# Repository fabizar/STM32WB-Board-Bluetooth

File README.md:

# KiCad Project: [STM32WB Board Bluetooth]

This is a hardware design project created using **KiCad**. It includes the schematic and PCB layout for a STM32 dev board.

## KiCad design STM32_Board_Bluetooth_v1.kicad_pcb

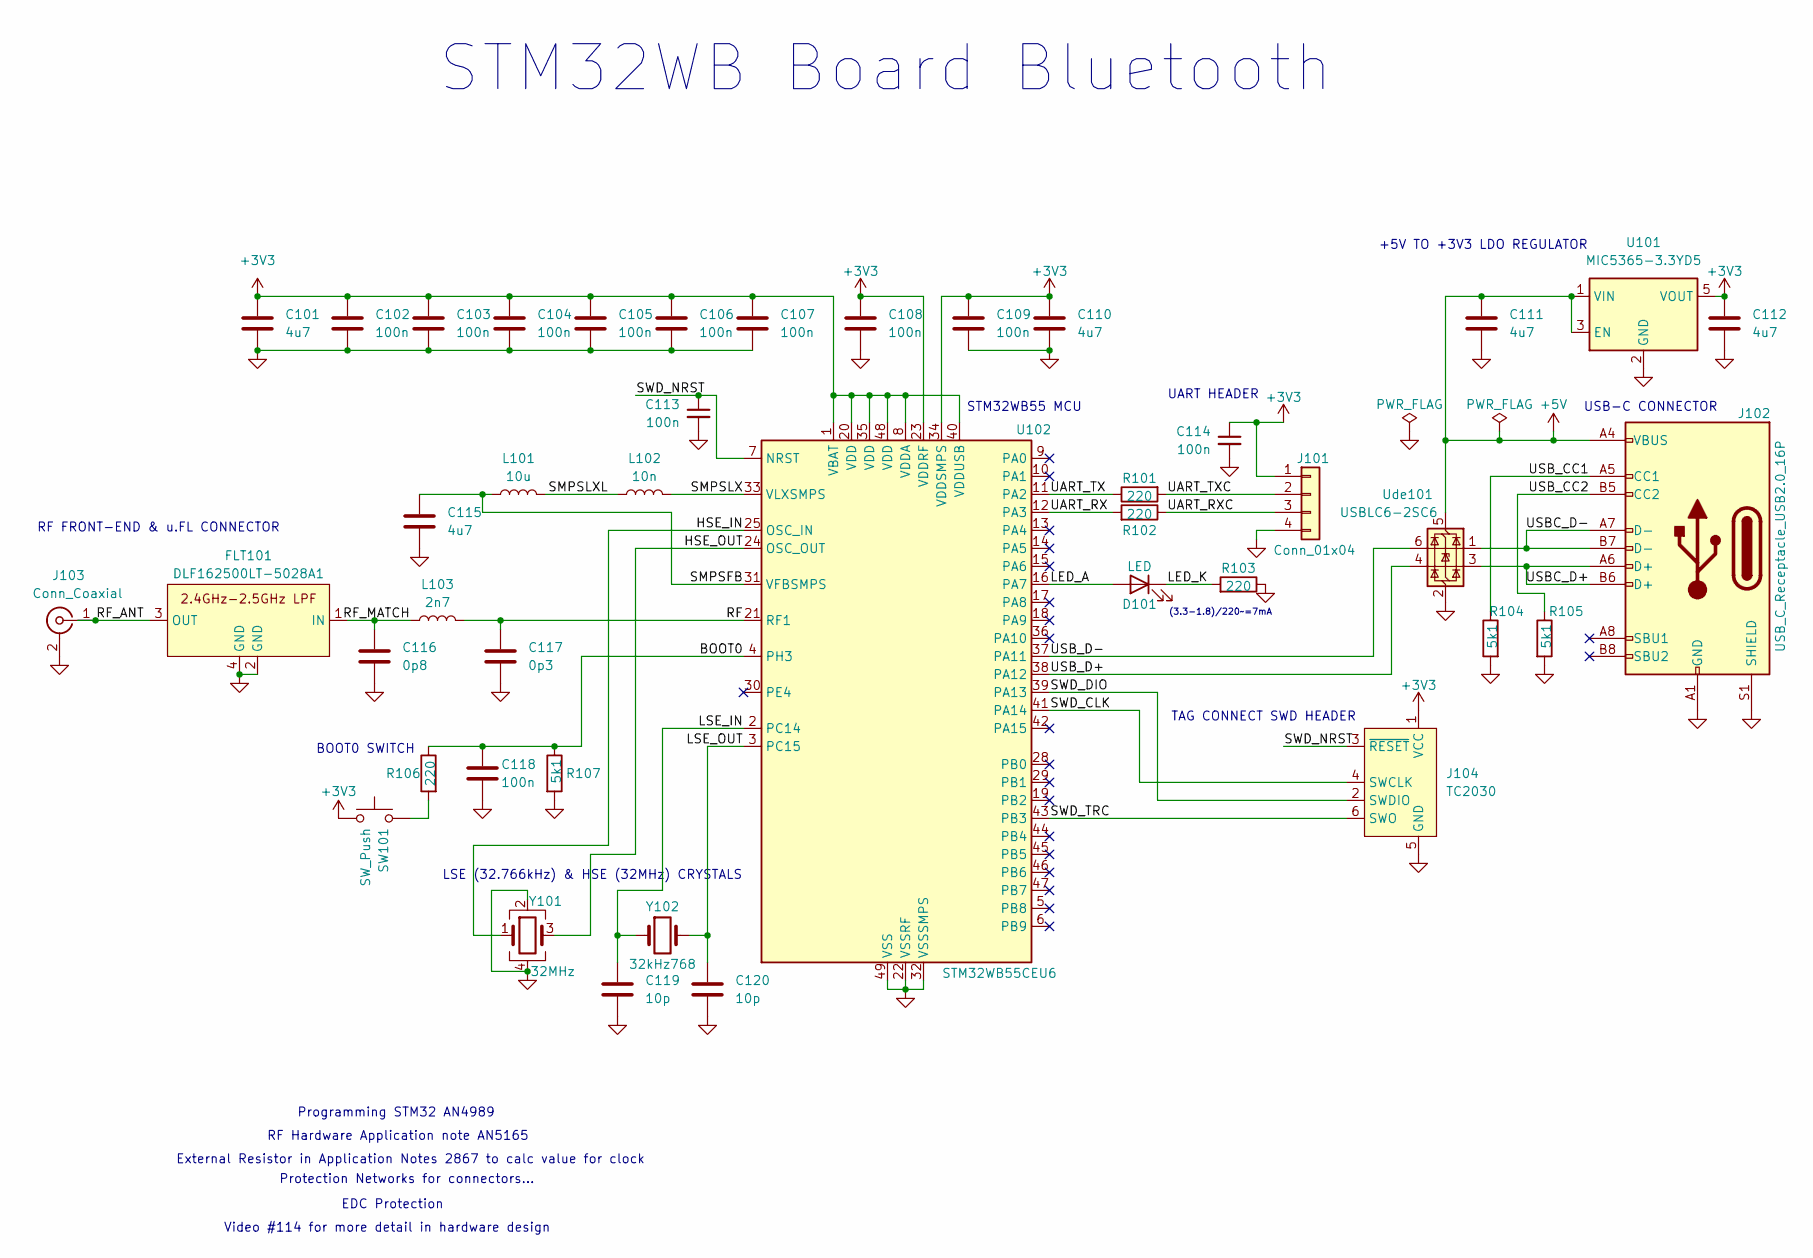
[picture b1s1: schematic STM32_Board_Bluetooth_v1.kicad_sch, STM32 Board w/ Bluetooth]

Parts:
C101, C110, C111, C112, C115: 4u7; C_0603_1608Metric
C102, C103, C104, C105, C106, C107, C108, C109, C113, C114, C118: 100n; C_0402_1005Metric
C116: 0p8; C_0402_1005Metric
C117: 0p3; C_0402_1005Metric
C119, C120: 10p; C_0402_1005Metric
D101: LED; LED_0402_1005Metric
FLT101: DLF162500LT-5028A1; DLT162500LT-5028A1
J101: Conn_01x04; Molex_PicoBlade_53048-0410_1x04_P1.25mm_Horizontal
J102: USB_C_Receptacle_USB2.0_16P; USB_C_Receptacle_GCT_USB4105-xx-A_16P_TopMnt_Horizontal
J103: Conn_Coaxial; U.FL_Hirose_U.FL-R-SMT-1_Vertical
J104: TC2030; Tag-Connect_TC2030-IDC-FP_2x03_P1.27mm_Vertical
L101: 10u; L_0805_2012Metric
L102: 10n; L_0402_1005Metric
L103: 2n7; L_0402_1005Metric
R101, R102, R103, R106: 220; R_0402_1005Metric
R104, R105, R107: 5k1; R_0402_1005Metric
SW101: SW_Push; SW_SPST_CK_RS282G05A3
U101: MIC5365-3.3YD5; SOT-23-5
U102: STM32WB55CEU6; QFN-48-1EP_7x7mm_P0.5mm_EP5.6x5.6mm
Ude101: USBLC6-2SC6; SOT-23-6
Y101: 32MHz; Crystal_SMD_2016-4Pin_2.0x1.6mm
Y102: 32kHz768; Crystal_SMD_2012-2Pin_2.0x1.2mm

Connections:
+3V3: C101.1, C102.1, C103.1, C104.1, C105.1, C106.1, C107.1, C108.1, C109.1, C110.1, C112.1, C114.1, J101.1, J104.1 (VCC), SW101.2, U101.5 (VOUT), U102.1 (VBAT), U102.8 (VDDA), U102.20 (VDD), U102.23 (VDDRF), U102.34 (VDDSMPS), U102.35 (VDD), U102.40 (VDDUSB), U102.48 (VDD)
+5V: C111.1, J102.A4 (VBUS), J102.A9 (VBUS), J102.B4 (VBUS), J102.B9 (VBUS), U101.1 (VIN), U101.3 (EN), Ude101.5 (VBUS)
/BOOT0: C118.1, R106.1, R107.1, U102.4 (PH3)
/HSE_IN: U102.25 (OSC_IN), Y101.1
/HSE_OUT: U102.24 (OSC_OUT), Y101.3
/LED_A: D101.2 (A), U102.16 (PA7)
/LED_K: D101.1 (K), R103.2
/LSE_IN: C119.1, U102.2 (PC14), Y102.1
/LSE_OUT: C120.1, U102.3 (PC15), Y102.2
/RF: C117.1, L103.2, U102.21 (RF1)
/RF_ANT: FLT101.3 (OUT), J103.1 (In)
/RF_MATCH: C116.1, FLT101.1 (IN), L103.1
/SMPSFB: C115.1, L101.1, U102.31 (VFBSMPS)
/SMPSLX: L102.2, U102.33 (VLXSMPS)
/SMPSLXL: L101.2, L102.1
/SWD_CLK: J104.4 (SWCLK), U102.41 (PA14)
/SWD_DIO: J104.2 (SWDIO), U102.39 (PA13)
/SWD_NRST: C113.1, J104.3 (~RESET), U102.7 (NRST)
/SWD_TRC: J104.6 (SWO), U102.43 (PB3)
/UART_RX: R102.2, U102.12 (PA3)
/UART_RXC: J101.3, R102.1
/UART_TX: R101.1, U102.11 (PA2)
/UART_TXC: J101.2, R101.2
/USBC_D+: J102.A6 (D+), J102.B6 (D+), Ude101.3 (I/O2)
/USBC_D-: J102.A7 (D-), J102.B7 (D-), Ude101.1 (I/O1)
/USB_CC1: J102.A5 (CC1), R104.1
/USB_CC2: J102.B5 (CC2), R105.1
/USB_D+: U102.38 (PA12), Ude101.4 (I/O2)
/USB_D-: U102.37 (PA11), Ude101.6 (I/O1)
GND: C101.2, C102.2, C103.2, C104.2, C105.2, C106.2, C107.2, C108.2, C109.2, C110.2, C111.2, C112.2, C113.2, C114.2, C115.2, C116.2, C117.2, C118.2, C119.2, C120.2, FLT101.2 (GND), FLT101.4 (GND), J101.4, J102.A1 (GND), J102.A12 (GND), J102.B1 (GND), J102.B12 (GND), J102.S1 (SHIELD), J103.2 (Ext), J104.5 (GND), R103.1, R104.2, R105.2, R107.2, U101.2 (GND), U102.22 (VSSRF), U102.32 (VSSSMPS), U102.49 (VSS), Ude101.2 (GND), Y101.2, Y101.4
unnamed: R106.2, SW101.1

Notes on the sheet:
RF FRONT-END & u.FL CONNECTOR
Video #114 for more detail in hardware design
+5V TO +3V3 LDO REGULATOR
EDC Protection
Programming STM32 AN4989
Protection Networks for connectors...
LSE (32.766kHz) & HSE (32MHz) CRYSTALS
UART HEADER
(3.3-1.8)/220~=7mA
USB-C CONNECTOR
STM32WB Board Bluetooth
STM32WB55 MCU
BOOT0 SWITCH
RF Hardware Application note AN5165
TAG CONNECT SWD HEADER
External Resistor in Application Notes 2867 to calc value for clock

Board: 4 copper layers, 42 parts (0 on the bottom side), 31 nets, no tracks yet.

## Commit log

2025-07-06 Add files via upload
    Schematic PDF
2025-07-06 Add files via upload
    Actual KiCad Schematic of project.
2025-07-07 KiCad Files Upload
